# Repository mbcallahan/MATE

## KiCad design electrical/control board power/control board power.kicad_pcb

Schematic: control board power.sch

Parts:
C1, C2: 10uF; C_0603_1608Metric_Pad1.05x0.95mm_HandSolder; Digikey part number 490-7198-1-ND
C3, C4, C19, C20: 2.2uF; C_1210_3225Metric_Pad1.42x2.65mm_HandSolder; Digikey part number 445-4497-1-ND
C5, C7: 1uF; C_0603_1608Metric_Pad1.05x0.95mm_HandSolder; Digikey part number 478-5010-1-ND
C6, C8: .1uF; C_0603_1608Metric_Pad1.05x0.95mm_HandSolder; Digikey part number 399-1100-1-ND
C9: 10pF; C_0603_1608Metric_Pad1.05x0.95mm_HandSolder; Digikey part number 732-7760-1-ND
C10: 2.2nF; C_0603_1608Metric_Pad1.05x0.95mm_HandSolder; Digikey part number 732-8003-1-ND
C11: 100pF; C_0603_1608Metric_Pad1.05x0.95mm_HandSolder; Digikey part number 732-7947-1-ND
C12, C13, C15, C16, C17, C18: 22uF; C_1210_3225Metric_Pad1.42x2.65mm_HandSolder; Digikey part number 1276-1855-1-ND
C14, C25, C26, C27: 330u; CP_Radial_D18.0mm_P7.50mm; Digikey part number 493-16707-ND
C21, C22: 0.1uF; C_0805_2012Metric_Pad1.15x1.40mm_HandSolder; Digikey part number 732-12244-1-ND
C23, C24: 10uF; C_1210_3225Metric_Pad1.42x2.65mm_HandSolder; Digikey part number 1276-3307-1-ND
D1: LED; LED_0603_1608Metric_Pad1.05x0.95mm_HandSolder_diode_mark; Digikey part number SML-D12U1WT86CT-ND
D2: LED; LED_0603_1608Metric_Pad1.05x0.95mm_HandSolder_diode_mark; Digikey part number 160-1446-1-ND
D3: LED; LED_0603_1608Metric_Pad1.05x0.95mm_HandSolder_diode_mark; Digikey part number 846-1178-2-ND
D4, D5: LED; LED_0603_1608Metric_Pad1.05x0.95mm_HandSolder_diode_mark; Digikey part number 1830-1071-1-ND
D8: LED; LED_0603_1608Metric_Pad1.05x0.95mm_HandSolder_diode_mark; Digikey part number 754-2180-1-ND
D9, D10: D_Small; D_SMC_Handsoldering_Diode_Mark; Digikey part number SMCJ150CALFCT-ND
J1: Conn_01x02; Molex_Mini-Fit_Jr_5566-02A_2x01_P4.20mm_Vertical; Digikey part number N/A
J2: 5V; PinHeader_1x02_P2.54mm_Vertical; Digikey part number N/A
J3: Barrel_Jack; CUI_PJ-002AH; Digikey part number CP-002AH-ND
J4: Switch_A; Molex_Mini-Fit_Jr_5566-02A_2x01_P4.20mm_Vertical; Digikey part number WM8360-ND
J5: Conn_01x03; Harwin_LTek-Male_03_P2.00mm_Vertical
J6: Power_Connector; Molex_Mini-Fit_Jr_5566-08A2_2x04_P4.20mm_Vertical; Digikey part number WM3803-ND
J7: Switch_A_High; Square_Pad_6mm; Digikey part number N/A
J8: Switch_B_High; Square_Pad_6mm; Digikey part number N/A
J9: Aux_1; Molex_Mini-Fit_Jr_5566-04A_2x02_P4.20mm_Vertical
J10: 48V_from_conversion; Molex_Mini-Fit_Jr_5566-02A_2x01_P4.20mm_Vertical; Digikey part number WM8360-ND
J11: Aux_2; Molex_Mini-Fit_Jr_5566-04A_2x02_P4.20mm_Vertical
J17: Switch_B; Molex_Mini-Fit_Jr_5566-02A_2x01_P4.20mm_Vertical; Digikey part number WM8360-ND
L1, L2: 33uH; L_Radial_D12.0mm_P6.00mm_MuRATA_1900R; Digikey part number 6100-330K-RC-ND
Q1, Q2: Q_NMOS_GDS; TO-252-3_2_Pin; Digikey part number BTS3046SDRATMA1CT-ND
R1: 330; R_0603_1608Metric_Pad1.05x0.95mm_HandSolder; Digikey part number CR0603-JW-331ELFCT-ND
R2, R12, R13: 150; R_0603_1608Metric_Pad1.05x0.95mm_HandSolder; Digikey part number RMCF0603JT150RCT-ND
R3: 9.4k; R_1206_3216Metric_Pad1.42x1.75mm_HandSolder; Digikey part number 408-1869-1-ND
R4, R5: 10k; R_0603_1608Metric_Pad1.05x0.95mm_HandSolder; Digikey part number N/A
R7: 100k; R_0603_1608Metric_Pad1.05x0.95mm_HandSolder; Digikey part number 311-100KHRCT-ND
R8: 4.02k; R_0603_1608Metric_Pad1.05x0.95mm_HandSolder; Digikey part number RMCF0603FT4K02CT-ND
R10: 5.11k; R_0603_1608Metric_Pad1.05x0.95mm_HandSolder; Digikey part number RMCF0603FT5K11CT-ND
R16: 2.7k; R_1206_3216Metric_Pad1.42x1.75mm_HandSolder; Digikey part number 408-1906-1-ND
TB1: Curtis_2010; Digikey part number 364-1381-ND
TB2: Curtis_2010; Digikey part number 364-1381-ND
U1: LD1117S33TR_SOT223; SOT-223-3_TabPin2; Digikey part number 497-1242-1-ND
U2, U3: LTC7103-LT7103; LTC7103_long_pads_hole; Digikey part number LTC7103HUHE#TRPBFCT-ND

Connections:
+3V3: C2.1, C25.1, J6.5, J9.3, J11.3, R2.2, U1.2 (VO)
+5V: C1.1, C12.1, C13.1, C14.1, C15.1, C16.1, C17.1, C18.1, J2.1, J6.6, J9.4, J11.4, L1.2, L2.2, R1.2, U1.3 (VI), U2.20, U3.10, U3.20; also elsewhere on the board
+24V: C26.1, J1.1, J1.2, J6.7, R16.1
+48V: C3.1, C4.1, C19.1, C20.1, C21.1, C22.1, C27.1, J3.1, J6.8, J10.1, J10.2, R3.1, U2.3, U2.30, U2.31, U2.32, U3.3, U3.30, U3.31, U3.32
/SWITCH_A: J5.1, Q1.1, R4.1, R12.2
/SWITCH_A_HIGH: C23.2, D9.1, J4.1, J7.1
/SWITCH_B: J5.2, Q2.1, R5.1, R13.2
/SWITCH_B_HIGH: C24.2, D10.1, J8.1, J17.1
GND: C1.2, C2.2, C3.2, C4.2, C5.2, C7.2, C9.2, C11.1, C12.2, C13.2, C14.2, C15.2, C16.2, C17.2, C18.2, C19.2, C20.2, C21.2, C22.2, C23.1, C24.1, C25.2, C26.2, C27.2, D1.1, D2.1, D3.1, D4.1, D5.1, D8.1, J2.2, J3.2, J5.3, J6.1, J6.2, J6.3, J6.4, J9.1, J9.2, J11.1, J11.2, Q1.3, Q2.3, R4.2, R5.2, R8.2, R10.2, U1.1 (GND), U2.6, U2.7, U2.11, U2.35, U2.36, U2.37, U3.6, U3.7, U3.11, U3.19, U3.35, U3.36, U3.37; also elsewhere on the board
unnamed: C5.1, U2.10, U2.21
unnamed: C6.1, U2.27
unnamed: C6.2, L1.1, U2.24, U2.25, U2.26
unnamed: C7.1, R7.2, U3.21
unnamed: C8.1, U3.27
unnamed: C8.2, L2.1, U3.24, U3.25, U3.26
unnamed: C9.1, U2.9
unnamed: C10.1, R10.1
unnamed: C10.2, C11.2, U2.16, U3.9
unnamed: D1.2, R1.1
unnamed: D2.2, R2.1
unnamed: D3.2, R3.2
unnamed: D4.2, R12.1
unnamed: D5.2, R13.1
unnamed: D8.2, R16.2
unnamed: D9.2, J4.2, Q1.2
unnamed: D10.2, J17.2, Q2.2
unnamed: R7.1, U3.12
unnamed: R8.1, U2.8
unnamed: U2.12, U3.13
unnamed: U2.15, U3.15

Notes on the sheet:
Power Indicators
Power
Check regulator is correct voltage
Check capacitor voltage ratings!!!
Look at Connor's 5V converter board to check component ratings, etc.
DO NOT CONNECT 12V AND 48V SIMUTANIOUSLY!!!!
Note: Stack terminal blocks

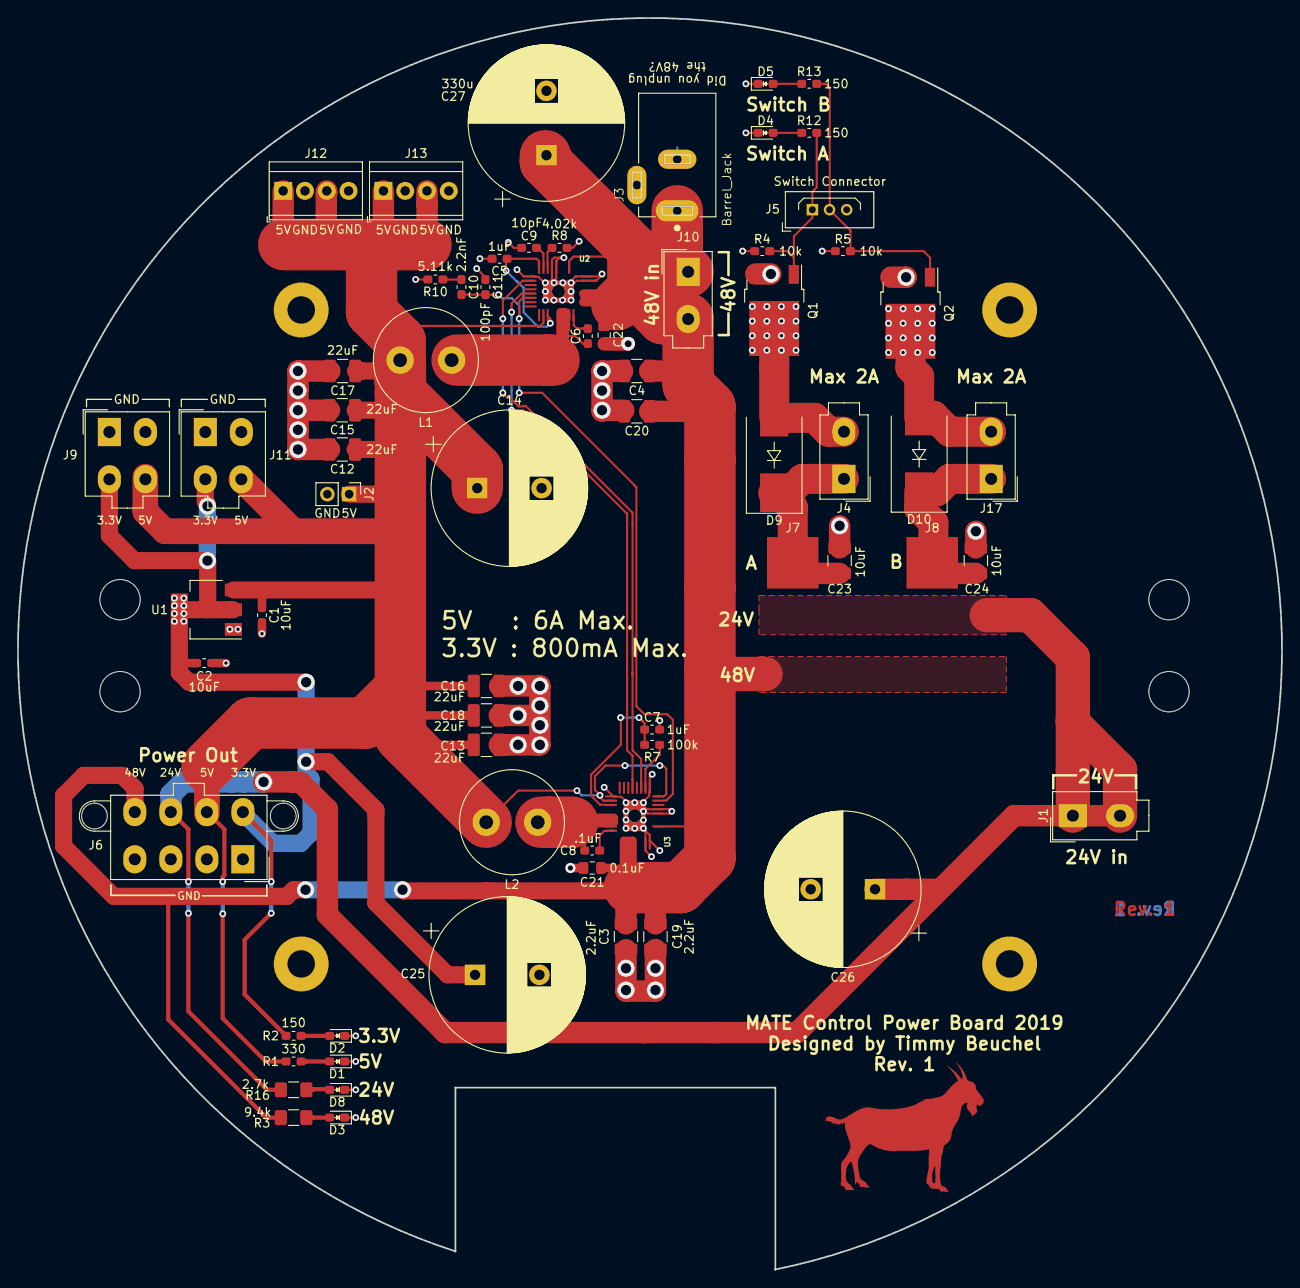
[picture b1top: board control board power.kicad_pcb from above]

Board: 2 copper layers, 147.3 x 145.8 mm, 68 parts (1 on the bottom side), 30 nets.

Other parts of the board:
J12, J13: Conn_01x04; TerminalBlock_TE_282834-4_1x04_P2.54mm_Horizontal

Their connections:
+5V: J12.1, J12.3, J13.1, J13.3; also elsewhere on the board
GND: J12.2, J12.4, J13.2, J13.4; also elsewhere on the board

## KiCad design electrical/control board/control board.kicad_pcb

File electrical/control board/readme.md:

## Control Board
The control board contains the main STM32 microcontroller, the IMU (inertial measurement unit, the accelerometer and gyroscope), the temperature and humidity sensor, and headers for the motor drivers.
### Sensors
<table>
  <tr>
    <th>Pin Name (chip)</th>
    <th>Description</th>
    <th>Pin Number (LPQF64)</th>
    <th>Pin Name (Microcontroller)</th>
  </tr>
  <tr>
    <td colspan="4">HIH6131<br></td>
  </tr>
  <tr>
    <td>SCL<br></td>
    <td>I2C Clock</td>
    <td>37</td>
    <td>PC6</td>
  </tr>
  <tr>
    <td>SDA</td>
    <td>I2C Data</td>
    <td>38</td>
    <td>PC7</td>
  </tr>
  <tr>
    <td colspan="4">BMI160</td>
  </tr>
  <tr>
    <td>SCL</td>
    <td>I2C Clock</td>
    <td>41</td>
    <td>PA8</td>
  </tr>
  <tr>
    <td>SDA</td>
    <td>I2C Data</td>
    <td>40<br></td>
    <td>PC9</td>
  </tr>
  <tr>
    <td colspan="4">ADM3061 (sensors)<br></td>
  </tr>
  <tr>
    <td>RO/RX</td>
    <td>Receive data<br></td>
    <td>43<br></td>
    <td>PA9</td>
  </tr>
  <tr>
    <td>RE</td>
    <td>Receive enable (active high)</td>
    <td>44</td>
    <td>PA11</td>
  </tr>
  <tr>
    <td>DE</td>
    <td>Transmit enable (active low)</td>
    <td>45</td>
    <td>PA12</td>
  </tr>
  <tr>
    <td>DI/TX</td>
    <td>Transmit Data</td>
    <td>42</td>
    <td>PA10</td>
  </tr>
  <tr>
    <td colspan="4">ADM3061 (misc.)</td>
  </tr>
  <tr>
    <td>RO/RX</td>
    <td>Receive data</td>
    <td>52</td>
    <td>PC11<br></td>
  </tr>
  <tr>
    <td>RE</td>
    <td>Receive enable (active high)</td>
    <td>2</td>
    <td>PC13<br></td>
  </tr>
  <tr>
    <td>DE</td>
    <td>Transmit enable (active low)</td>
    <td>3</td>
    <td>PC14</td>
  </tr>
  <tr>
    <td>DI/TX</td>
    <td>Transmit Data</td>
    <td>51</td>
    <td>PC10</td>
  </tr>
</table>

The control board also has four analog inputs that can measure the voltage of
all four nominal voltages present on the ROV:

| Nominal Voltage (V) | Analog Input Voltage at Nominal Voltage (V) | Pin Number (LQFP64) | Pin Name |
|---------------------|---------------------------------------------|---------------------|----------|
| 3.3                 | 2.8                                         | 8                   | PC0      |
| 5                   | 2.727                                       | 9                   | PC1      |
| 24                  | 1.485                                       | 27                  | PB1      |
| 48                  | 1.6679                                      | 10                  | PC2      |

### Motors
The control board supports up to 8 motors driven by a direct PWM signal.
The motor drivers we have use a PWM input at 50Hz, with time highs from 1100us to 1900us.

| Motor | Pin Number (LQFP64) | Pin Name |
|-------|---------------------|----------|
| 1     | 4                   | PC15     |
| 2     | 62                  | PB9      |
| 3     | 61                  | PB8      |
| 4     | 57                  | PB5      |
| 5     | 56                  | PB4      |
| 6     | 54                  | PD2      |
| 7     | 53                  | PC12     |
| 8     | 50                  | PA15     |

### Low side switches
The control board as 5 outputs designated for low side switches, however, the
power board only has two.
The headers will be configured to send the signals from switches A and B to the
low side switches on the board,
and signals for switches C, D, and E are unassigned at the moment. The switches
are a single digital output, active high.

| Switch | Pin Number (LQFP64) | Pin Name |
|--------|---------------------|----------|
| A      | 29                  | PB10     |
| B      | 33                  | PB12     |
| C      | 34                  | PB13     |
| D      | 35                  | PB14     |
| E      | 36                  | PB15     |

### LEDs
The control board has two power indicator LEDs. The yellow LED, D7, lights up
whenever voltage is present on the +3.3V line. The green LED, D8, lights up when
voltage is present in the 5V line. This LED will not light up when the board
is powered of the USB port unless the jumpers are configured to connect USB +5V
to board +5V (see below).

There are also six configurable LEDs. Three are connected to the Odroid/Raspberry
Pi, and three are connected to the STM32 according to the tables. The LEDs are
active high.

Odroid/Raspberry Pi LEDS:

| LED Color | Reference Designator | Pin Number (LQFP64) | Pin Name |
|-----------|----------------------|---------------------|----------|
| Red       | D1                   | 16                  | PA2      |
| Yellow    | D2                   | 17                  | PA3      |
| Green     | D3                   | 20                  | PA4      |

STM32 LEDs:

| LED Color | Reference Designator | Pin Number (LQFP64) | Pin Name |
|-----------|----------------------|---------------------|----------|
| Red       | D1                   | 16                  | PA2      |
| Yellow    | D2                   | 17                  | PA3      |
| Green     | D3                   | 20                  | PA4      |

### Jumper Configuration
A single 2.54mm pitch header jumper is used to toggle between having the USB
input power the 3.3V line only or the 3.3V line and the 5V line. If connecting
the jumper, make sure the USB power supply can support the entire board. In
particular, the Odroid or Raspberry Pi can use up to 3 amps. To connect the
USB input to the 5V line, connect the jumper to header J17. Header J18 is not
connected to anything and has been provided to store that jumper.

### Known Issues
* The IMU was not soldered very well and may not work at all or work intermittently.

### Things to be fixed
* Use an IMU that can actually be soldered

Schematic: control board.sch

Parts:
C1: .22uF; C_0603_1608Metric_Pad1.05x0.95mm_HandSolder; Digikey part number 490-8017-1-ND
C2, C3: 30pF; C_0603_1608Metric_Pad1.05x0.95mm_HandSolder; Digikey part number 1276-1021-1-ND
C4, C17: .1uF; C_0603_1608Metric_Pad1.05x0.95mm_HandSolder; Digikey part number 1276-1005-1-ND
C5, C6, C7, C8, C9, C10, C11, C12: 100nF; C_0603_1608Metric_Pad1.05x0.95mm_HandSolder; Digikey part number 1276-1005-1-ND
C13, C14: 1uF; C_0603_1608Metric_Pad1.05x0.95mm_HandSolder; Digikey part number 1276-1102-1-ND
C15, C16: 10uF; C_0603_1608Metric_Pad1.05x0.95mm_HandSolder; Digikey part number 490-10728-1-ND
C18: 2.2uF; C_0603_1608Metric_Pad1.05x0.95mm_HandSolder; Digikey part number 490-10731-1-ND
D1, D4: LED-RED; LED_0603_1608Metric_Pad1.05x0.95mm_HandSolder; Digikey part number SML-D12U1WT86CT-ND
D2, D5, D7: LED-YELLOW; LED_0603_1608Metric_Pad1.05x0.95mm_HandSolder; Digikey part number 160-1448-1-ND
D3, D6, D8: LED-GREEN; LED_0603_1608Metric_Pad1.05x0.95mm_HandSolder; Digikey part number 160-1446-1-ND
J1: analog_extra; PinHeader_1x02_P2.54mm_Vertical; Digikey part number HDR100IMP40M-G-V-TH-ND
J2: Programming_Header; PinHeader_1x06_P2.54mm_Vertical; Digikey part number HDR100IMP40M-G-V-TH-ND
J3: USB_B; USB_B_OST_USB-B1HSxx_Horizontal; Digikey part number UE27BC54130-ND
J4: datamate_sensors; Harwin_LTek-Male_04_P2.00mm_Vertical; Digikey part number 952-1071-5-ND
J5: Motor_1; Harwin_LTek-Male_03_P2.00mm_Vertical; Digikey part number 952-1070-5-ND‎
J6: datamate_misc; Harwin_LTek-Male_04_P2.00mm_Vertical; Digikey part number 952-1071-5-ND
J7: Power_Connector; Molex_Mini-Fit_Jr_5566-08A2_2x04_P4.20mm_Vertical; Digikey part number WM3803-ND
J8: Power_Header; 1x2 individual header; Digikey part number HDR100IMP40M-G-V-TH-ND
J9: Switch_Connector; Harwin_LTek-Male_06_P2.00mm_Vertical; Digikey part number 952-1072-5-ND
J10: Motor_2; Harwin_LTek-Male_03_P2.00mm_Vertical; Digikey part number 952-1070-5-ND‎
J11: Motor_3; Harwin_LTek-Male_03_P2.00mm_Vertical; Digikey part number 952-1070-5-ND‎
J12: Motor_4; Harwin_LTek-Male_03_P2.00mm_Vertical; Digikey part number 952-1070-5-ND‎
J13: Motor_5; Harwin_LTek-Male_03_P2.00mm_Vertical; Digikey part number 952-1070-5-ND‎
J14: Motor_6; Harwin_LTek-Male_03_P2.00mm_Vertical; Digikey part number 952-1070-5-ND‎
J15: Motor_7; Harwin_LTek-Male_03_P2.00mm_Vertical; Digikey part number 952-1070-5-ND‎
J16: Motor_8; Harwin_LTek-Male_03_P2.00mm_Vertical; Digikey part number 952-1070-5-ND‎
J17: USB_to_5V; PinHeader_1x02_P2.54mm_Vertical; Digikey part number HDR100IMP40M-G-V-TH-ND
J18: Storage; PinHeader_1x02_P2.54mm_Vertical; Digikey part number HDR100IMP40M-G-V-TH-ND
P1: ODROID-C2; Digikey part number SAM9012-ND
Q2: DTC114E; SOT-23; Digikey part number DTC114EET1GOSCT-ND
R1, R2: 2.2k; R_0603_1608Metric_Pad1.05x0.95mm_HandSolder; Digikey part number A130093CT-ND
R3, R4, R7, R13: 10k; R_0603_1608Metric_Pad1.05x0.95mm_HandSolder; Digikey part number CR0603-JW-103ELFCT-ND
R5, R9, R10, R11, R17, R18, R19: 68; R_0603_1608Metric_Pad1.05x0.95mm_HandSolder; Digikey part number RMCF0603JT68R0CT-ND
R6: 180; R_0603_1608Metric_Pad1.05x0.95mm_HandSolder
R8: 56k; R_0603_1608Metric_Pad1.05x0.95mm_HandSolder; Digikey part number RMCF0603JT56K0CT-ND
R12, R15: 100k; R_0603_1608Metric_Pad1.05x0.95mm_HandSolder; Digikey part number CR0603-JW-104ELFCT-ND
R14: 12k; R_0603_1608Metric_Pad1.05x0.95mm_HandSolder; Digikey part number CR0603-JW-123ELFCT-ND
R16: 3.6k; R_0603_1608Metric_Pad1.05x0.95mm_HandSolder; Digikey part number RMCF0603JT3K60CT-ND
R20: 6.6k; R_0603_1608Metric_Pad1.05x0.95mm_HandSolder; Digikey part number A129698CT-ND
SW1: SW_Push; SW_SPST_PTS645; Digikey part number CKN9112CT-ND
U1: STM32F446RETx; LQFP-64_10x10mm_P0.5mm_handsolder; Digikey part number 497-15376-ND
U2: HIH6131-021; SOIC-8_3.9x4.9mm_P1.27mm; Digikey part number 480-3652-1-ND
U3: LD1117S33TR_SOT223; SOT-223-3_TabPin2; Digikey part number 497-1242-1-ND
U4, U6: ADM3061; TSSOP-8_3x3mm_P0.65mm; Digikey part number ADM3061EARMZ-ND
U5: BMI160; LGA-14_3x2.5mm_P0.5mm_pads_shrunk; Digikey part number 828-1057-1-ND
Y1: 8Mhz; Crystal_HC49-U_Vertical; Digikey part number CTX917-ND‎

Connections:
+3V3: C1.2, C4.2, C5.2, C6.2, C7.2, C8.2, C9.2, C10.2, C11.1, C12.1, C13.1, C14.1, C16.1, J2.1, J7.5, J8.2, R1.1, R2.1, R3.2, R4.2, R5.2, R7.1, U1.1 (VBAT), U1.13 (VDDA), U1.19 (VDD), U1.32 (VDD), U1.48 (VDD), U1.64 (VDD), U2.8, U3.2 (VO), U4.8, U5.5, U5.8, U5.12, U6.8
+5V: J7.6, J17.1, P1.2, P1.4, R6.2, R13.1
+24V: J7.7, R12.1
+48V: J4.1, J6.1, J7.8, R15.1
/3.3V_MEASURE: R7.2, R8.1, U1.8 (PC0)
/5V_MEASURE: R13.2, R14.1, U1.9 (PC1)
/24V_MEASURE: R12.2, R20.1, U1.27 (PB1)
/48V_MEASURE: R15.2, R16.1, U1.10 (PC2)
/CURRENT_MEASURE: U1.11 (PC3)
/HIH_SCL: R1.2, U1.37 (PC6), U2.3
/HIH_SDA: R2.2, U1.38 (PC7), U2.4
/ICM_SCL: R4.1, U1.41 (PA8), U5.13
/ICM_SDA: R3.1, U1.40 (PC9), U5.14
/JTDO: J2.6, U1.55 (PB3)
/MISC_DE: U1.3 (PC14), U6.3
/MISC_RE: U1.2 (PC13), U6.2
/MISC_RX: U1.52 (PC11), U6.1
/MISC_TX: U1.51 (PC10), U6.4
/MOTOR_1: J5.3, U1.4 (PC15)
/MOTOR_2: J10.3, U1.62 (PB9)
/MOTOR_3: J11.3, U1.61 (PB8)
/MOTOR_4: J12.3, U1.57 (PB5)
/MOTOR_5: J13.3, U1.56 (PB4)
/MOTOR_6: J14.3, U1.54 (PD2)
/MOTOR_7: J15.3, U1.53 (PC12)
/MOTOR_8: J16.3, U1.50 (PA15)
/NRST: C17.1, J2.5, Q2.3, SW1.1, U1.7 (NRST)
/ODROID_RX: P1.10, U1.14 (PA0)
/ODROID_TX: P1.8, U1.15 (PA1)
/SENSOR_DE: U1.45 (PA12), U4.3
/SENSOR_RE: U1.44 (PA11), U4.2
/SENSOR_RX: U1.43 (PA10), U4.1
/SENSOR_TX: U1.42 (PA9), U4.4
/STM_RESET: P1.7, Q2.1
/SWCLK: J2.2, U1.49 (PA14)
/SWDIO: J2.4, U1.46 (PA13)
/SWITCH_A: J9.6, U1.29 (PB10)
/SWITCH_B: J9.5, U1.33 (PB12)
/SWITCH_C: J9.4, U1.34 (PB13)
/SWITCH_D: J9.3, U1.35 (PB14)
/SWITCH_E: J9.2, U1.36 (PB15)
/USART1_RX: U1.59 (PB7)
/USART1_TX: U1.58 (PB6)
unnamed: C2.1, U1.5 (PH0), Y1.1
unnamed: C3.1, U1.6 (PH1), Y1.2
unnamed: C4.1, U2.1
unnamed: C15.1, J3.1, J17.2, U3.3 (VI)
unnamed: C18.1, U1.30 (VCAP_1)
unnamed: D1.2, R9.2
unnamed: D2.2, R10.1
unnamed: D3.2, R11.1
unnamed: D4.2, R17.1
unnamed: D5.2, R18.1
unnamed: D6.2, R19.1
unnamed: D7.2, R5.1
unnamed: D8.2, R6.1
unnamed: J1.2, U1.24 (PC4)
unnamed: J4.2, U4.7
unnamed: J4.3, U4.6
unnamed: J6.2, U6.7
unnamed: J6.3, U6.6
unnamed: P1.33, R17.2
unnamed: P1.35, R18.2
unnamed: P1.37, R19.2
unnamed: R9.1, U1.16 (PA2)
unnamed: R10.2, U1.17 (PA3)
unnamed: R11.2, U1.20 (PA4)

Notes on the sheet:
USART6_TX
USART6_RX
UART4 : Odroid UART2 : Motors UART1 : Sensors UART3 : Misc
Voltage Monitering
Consider moving to power board
Add header space for current measurement
Not connected to +5V to avoid overcurrent on USB port attempting to power odroid
Consider adding switch instead

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
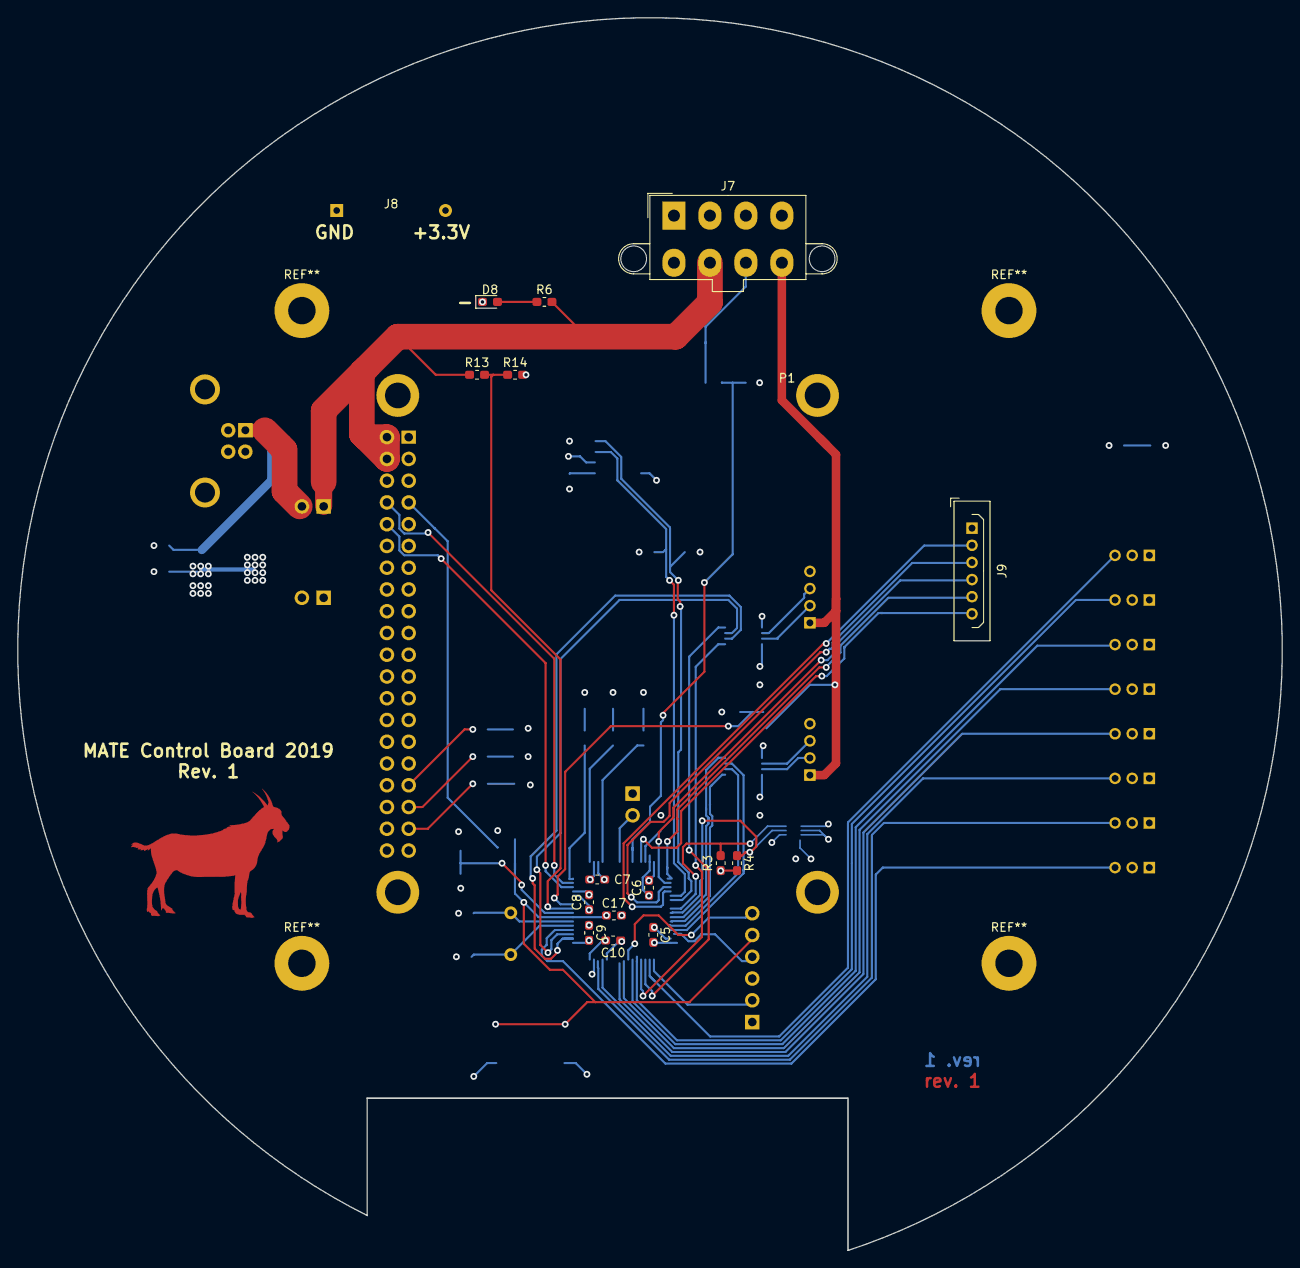
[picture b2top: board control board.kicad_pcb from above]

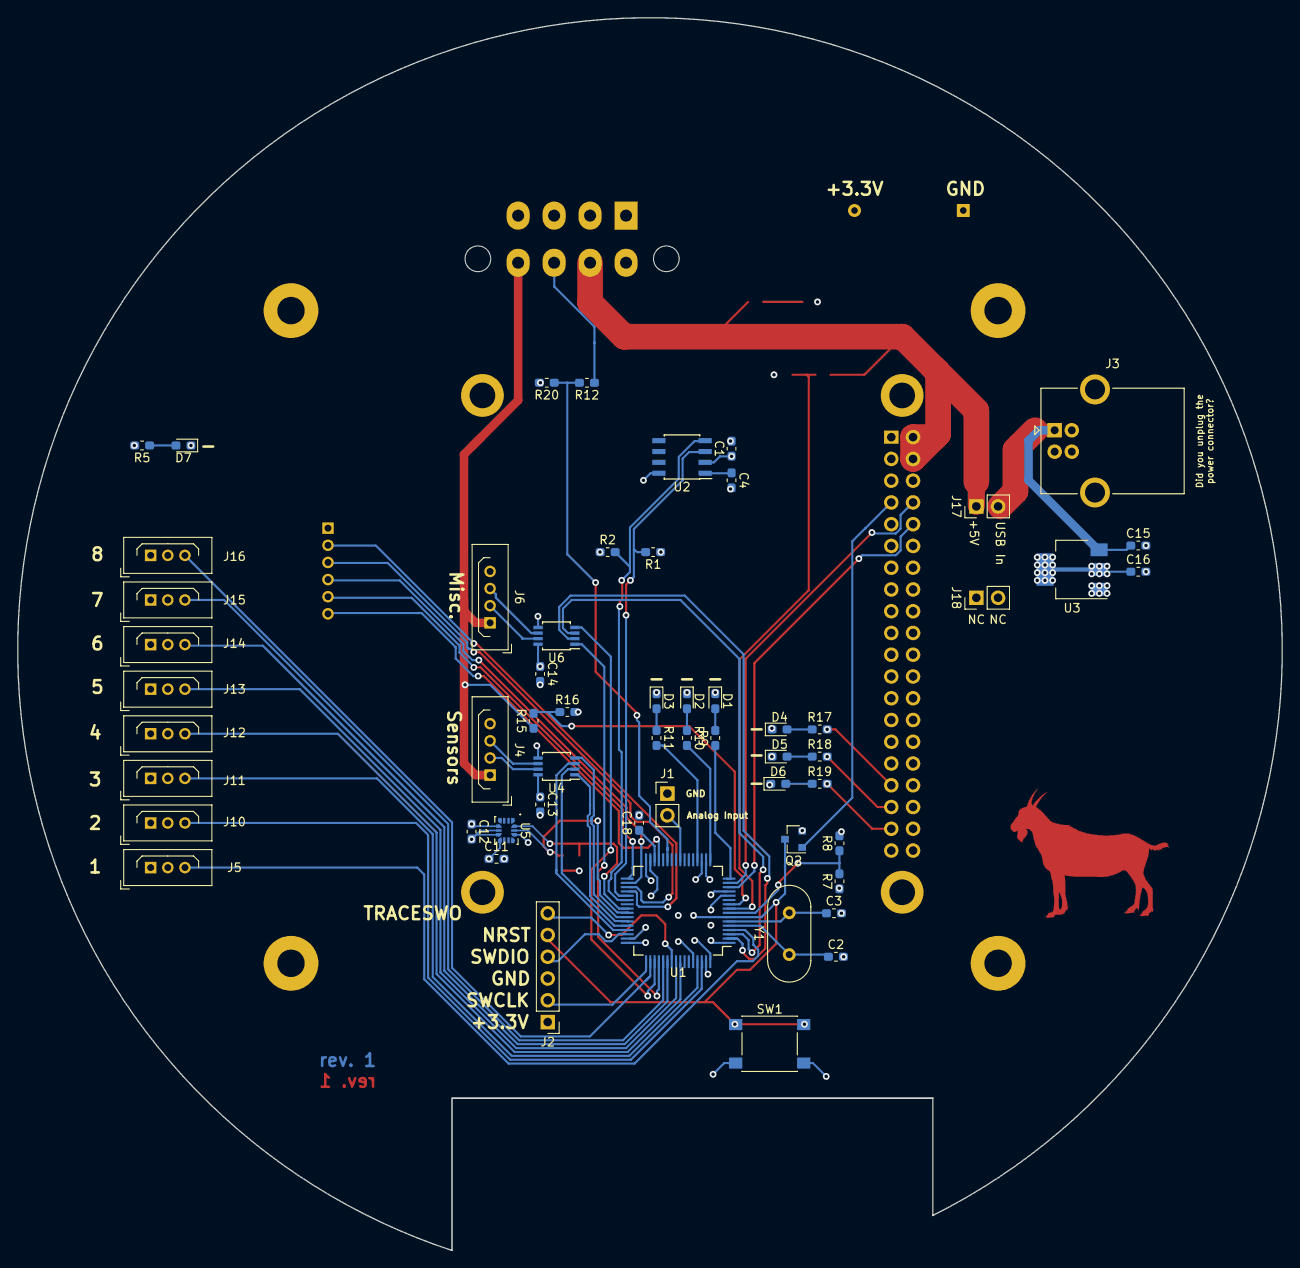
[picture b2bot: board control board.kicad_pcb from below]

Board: 4 copper layers, 147.6 x 143.9 mm, 74 parts (57 on the bottom side), 65 nets.

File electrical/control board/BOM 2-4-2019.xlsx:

C1 | .22uF | Capacitor_SMD:C_0603_1608Metric_Pad1.05x0.95mm_HandSolder | 490-8017-1-ND | 1
> C2, C3 | 30pF | Capacitor_SMD:C_0603_1608Metric_Pad1.05x0.95mm_HandSolder | 1276-1021-1-ND | 2
> C4, C17 | .1uF | Capacitor_SMD:C_0603_1608Metric_Pad1.05x0.95mm_HandSolder | 1276-1005-1-ND | 2
> C5 - C12 | 100nF | Capacitor_SMD:C_0603_1608Metric_Pad1.05x0.95mm_HandSolder | 1276-1005-1-ND | 8
> C13, C14 | 1uF | Capacitor_SMD:C_0603_1608Metric_Pad1.05x0.95mm_HandSolder | 1276-1102-1-ND | 2
> C15, C16 | 10uF | Capacitor_SMD:C_0603_1608Metric_Pad1.05x0.95mm_HandSolder | 490-10728-1-ND | 2
C18 | 2.2uF | Capacitor_SMD:C_0603_1608Metric_Pad1.05x0.95mm_HandSolder | 490-10731-1-ND | 1
> D1, D4 | LED-RED | LED_SMD:LED_0603_1608Metric_Pad1.05x0.95mm_HandSolder | SML-D12U1WT86CT-ND | 2
> D2, D5 | LED-YELLOW | LED_SMD:LED_0603_1608Metric_Pad1.05x0.95mm_HandSolder | 160-1448-1-ND | 2
> D3, D6 | LED-GREEN | LED_SMD:LED_0603_1608Metric_Pad1.05x0.95mm_HandSolder | 160-1446-1-ND | 2
J1 | analog_extra | Connector_PinHeader_2.54mm:PinHeader_1x02_P2.54mm_Vertical | HDR100IMP40M-G-V-TH-ND | 1
J2 | Programming_Header | Connector_PinHeader_2.54mm:PinHeader_1x06_P2.54mm_Vertical | HDR100IMP40M-G-V-TH-ND | 1
J3 | USB_B | Connector_USB:USB_B_OST_USB-B1HSxx_Horizontal | UE27BC54130-ND | 1
J4 | datamate_sensors | Connector_Harwin:Harwin_LTek-Male_04_P2.00mm_Vertical | 952-1071-5-ND | 1
J5 | Motor_1 | Connector_Harwin:Harwin_LTek-Male_03_P2.00mm_Vertical | 952-1070-5-ND‎ | 1
J6 | datamate_misc | Connector_Harwin:Harwin_LTek-Male_04_P2.00mm_Vertical | 952-1071-5-ND | 1
J7 | Power_Connector | Connector_Molex:Molex_Mini-Fit_Jr_5566-08A2_2x04_P4.20mm_Vertical | WM3803-ND | 1
J8 | Power_Header | footprints:1x2 individual header | HDR100IMP40M-G-V-TH-ND | 1
J9 | Switch_Connector | Connector_Harwin:Harwin_LTek-Male_06_P2.00mm_Vertical | 952-1072-5-ND | 1
J10 | Motor_2 | Connector_Harwin:Harwin_LTek-Male_03_P2.00mm_Vertical | 952-1070-5-ND‎ | 1
J11 | Motor_3 | Connector_Harwin:Harwin_LTek-Male_03_P2.00mm_Vertical | 952-1070-5-ND‎ | 1
J12 | Motor_4 | Connector_Harwin:Harwin_LTek-Male_03_P2.00mm_Vertical | 952-1070-5-ND‎ | 1
J13 | Motor_5 | Connector_Harwin:Harwin_LTek-Male_03_P2.00mm_Vertical | 952-1070-5-ND‎ | 1
J14 | Motor_6 | Connector_Harwin:Harwin_LTek-Male_03_P2.00mm_Vertical | 952-1070-5-ND‎ | 1
J15 | Motor_7 | Connector_Harwin:Harwin_LTek-Male_03_P2.00mm_Vertical | 952-1070-5-ND‎ | 1
J16 | Motor_8 | Connector_Harwin:Harwin_LTek-Male_03_P2.00mm_Vertical | 952-1070-5-ND‎ | 1
J17 | USB_to_5V | Connector_PinHeader_2.54mm:PinHeader_1x02_P2.54mm_Vertical | HDR100IMP40M-G-V-TH-ND | 1
J18 | Storage | Connector_PinHeader_2.54mm:PinHeader_1x02_P2.54mm_Vertical | HDR100IMP40M-G-V-TH-ND | 1
P1 | ODROID-C2 | footprints:ODROID-C2 | SAM9012-ND | 1
Q2 | DTC114E | Package_TO_SOT_SMD:SOT-23 | DTC114EET1GOSCT-ND | 1
> R1, R2 | 2.2k | Resistor_SMD:R_0603_1608Metric_Pad1.05x0.95mm_HandSolder | A130093CT-ND | 2
> R3 - R13 | 10k | Resistor_SMD:R_0603_1608Metric_Pad1.05x0.95mm_HandSolder | CR0603-JW-103ELFCT-ND | 4
R8 | 56k | Resistor_SMD:R_0603_1608Metric_Pad1.05x0.95mm_HandSolder | RMCF0603JT56K0CT-ND | 1
> R9 - R19 | 220 | Resistor_SMD:R_0603_1608Metric_Pad1.05x0.95mm_HandSolder | A130087CT-ND | 6
R14 | 12k | Resistor_SMD:R_0603_1608Metric_Pad1.05x0.95mm_HandSolder | CR0603-JW-123ELFCT-ND | 1
R15 | 100k | Resistor_SMD:R_0603_1608Metric_Pad1.05x0.95mm_HandSolder | CR0603-JW-104ELFCT-ND | 1
R16 | 3.6k | Resistor_SMD:R_0603_1608Metric_Pad1.05x0.95mm_HandSolder | RMCF0603JT3K60CT-ND | 1
SW1 | SW_Push | Button_Switch_SMD:SW_SPST_PTS645 | PTS645SM43SMTR92 LFS | 1
U1 | STM32F446RETx | footprints:LQFP-64_10x10mm_P0.5mm_handsolder | 497-15376-ND | 1
U2 | HIH6131-021 | Package_SO:SOIC-8_3.9x4.9mm_P1.27mm | 480-3652-1-ND | 1
U3 | LD1117S33TR_SOT223 | Package_TO_SOT_SMD:SOT-223-3_TabPin2 | 497-1242-1-ND | 1
U5 | BMI160 | Package_LGA:LGA-14_3x2.5mm_P0.5mm_LayoutBorder3x4y | 828-1057-1-ND | 1
> U4, U6 | ADM3061 | Package_SO:TSSOP-8_3x3mm_P0.65mm | ADM3061EARMZ-ND | 2
Y1 | 8Mhz | Crystal:Crystal_HC49-U_Vertical | CTX917-ND‎ | 1
 |  | 6 wire ribbon cable | 1568-1938-ND | 1
 |  | Molex cable | WM8399-ND | 2
 |  | Datamate female | 952-1764-ND | 8
 |  | Jumper | S9337-ND | 1

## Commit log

2018-12-06 initial commit 2
2018-12-10 Added old code
2018-12-10 fixed newlines
2018-12-23 added controlboard
2018-12-23 removed motor communications
2018-12-23 new interface with motor drivers
2018-12-24 stuff
2018-12-24 deleted previous board
2018-12-24 moved power section of control board into a seperate project
2018-12-24 made a mess, then fixed it
2018-12-24 transfered power section to a new project
    for real this time
2018-12-25 Finally got the correct board outline in Kicad
2018-12-25 the correct board outline is now in the correct project
    For real this time, I promise
2018-12-25 some work on board
2018-12-25 Added footprint for power connector
2018-12-25 Moved current measurement to power board
2018-12-25 forgot to remove current measurement from pcb
2018-12-26 routed voltage measurement
2018-12-26 found a crystal
2018-12-27 Found parts for LEDs
2018-12-27 leds are sort of aded
2018-12-27 destoryed a lot of stuff around the microcontroller
2018-12-27 created hand solder footprint for microcontoller
2018-12-27 Changed pins on motors
2018-12-28 board is mostly routed
2018-12-28 control board is almost finished
2018-12-28 added low side switches to control board power
2018-12-30 made a footprint with long pads and a hole in the middle
2018-12-30 made a mess
2018-12-30 fixed the mess
2018-12-31 more stuff
2018-12-31 found a part for the barrel jack
2019-01-08 found parts for most of the stuff on the control board
2019-01-08 replaced the footprints of the data headers
2019-01-08 replaced the motor headers
2019-02-01 started making control board 2 layer
2019-02-01 capacitors are no longer in the microcontoller
2019-02-01 somewhat defragmented ground plane
2019-02-01 finished converting to 2 layer board
2019-02-02 capacitors are no longer in microcontroller
2019-02-02 created BMI160 symbol
2019-02-02 replaced sensor with BMI160
2019-02-02 routed new acceleration sensor
2019-02-02 placed mounting holes (m3 for now)
2019-02-02 added usb port and linear regulator
2019-02-02 moved motor headers
2019-02-02 replaced humidity sensor with one that exists
2019-02-02 mostly finished routing control board
2019-02-02 added capacitors to linear regulator
2019-02-02 Added pads to access internal layers
2019-02-02 Marked diode polarity
2019-02-02 added reset button
2019-02-02 connected stuff
2019-02-03 Added low side switch connector
2019-02-03 rerouted some things
2019-02-03 cleaned up tracks and vias
2019-02-03 Fixed solder mask distance
2019-02-03 labelled stuff
2019-02-03 control board should be ready to order
2019-02-03 Found some part numbers
2019-02-03 Found all part numbers
2019-02-03 Saved the addition of part numbers this time
2019-02-04 tweaked usb port
2019-02-05 Added power leds and bugfixes
2019-02-05 Added power indicators
2019-02-05 Added 24V measurement
2019-02-05 Found parts
2019-02-05 Generated gerber files
2019-02-06 Fixed trace seperatation
2019-02-06 Added some connectors to power board
2019-02-06 Added footprints for connectors
2019-02-06 power distribution board now has correct outline and mounting holes
2019-02-07 changed footprint for motor headers
2019-02-07 routed things
2019-02-07 assigned part number and footprint to transistors
2019-02-07 routed stuff
2019-02-08 Added thermal vias to switches, just in case
2019-02-08 Moved motor connectors
2019-02-08 added leds for low side switches
2019-02-08 added vias to regulator footprint
2019-02-08 changed nano-fit footprint to have sort-of not intersecting pads
2019-02-08 Created terminal block symbol and footprint
2019-02-09 Created symbol and footprint for other terminal strip
2019-02-09 replaced motor headers with mounting point for terminal block
2019-02-10 Rerouted the second regulator
2019-02-11 Found some parts
2019-02-11 Making the low side switches beefier
2019-02-11 Added flyback diodes on low side switches
2019-02-11 Moved indicator leds
2019-02-11 Switched location of low side switches
2019-02-12 added diode marks to diodes
2019-02-12 Added values for resistors
2019-02-12 Added some part numbers
2019-02-12 finished finding part numbers
2019-02-12 fixed 3.3v regulator part number
2019-02-13 fixed regulator part number
2019-02-16 Removed 2 low side switches
2019-02-16 Added 2 extra power connectors
2019-02-16 Added parts to board
2019-02-16 fixed unconnected parts
2019-02-16 Removed most of the via in pads
2019-02-27 odroid footprint now has correct pad dimentions
2019-03-08 Removed current measurement from power board
2019-03-09 Lots of important stuff
2019-03-12 Added cutout for cables to pass by
2019-03-12 Control power board ordered
2019-03-25 Created primative documentation for control board
    Subject to change where future tense is present
2019-03-28 tweaked silkscreen and re-exported gerbers
2019-03-28 added more documentation to the control board
2019-08-25 docs
2019-09-26 Create Schedule Notes
2019-09-26 Create STManalysis
    an explanation of my pitiful attempt to understand the STM
